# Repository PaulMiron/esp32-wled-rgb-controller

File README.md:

# ESP32 WLED RGB LED Controller

A simple controller board for **12V analog RGB LED strips** (non-addressable, common anode), built around an **ESP32 DevKitC** running **[WLED](https://kno.wled.ge/)**. It supports Wi-Fi control from the WLED app/web UI and an **IR remote** via an onboard IR receiver header.

| Assembled board | Schematic | PCB render |
|---|---|---|
|  |  |  |

## Features

- Controls 12V RGB LED strips (3 PWM channels)
- ESP32 DevKitC socketed on female headers (easy to replace/reflash)
- Logic-level MOSFETs (IRLZ44N) driven directly from 3.3V GPIO
- IR receiver input for standard 24/44-key RGB remotes
- Single 12V DC input (barrel jack); 5V for the ESP32 from an external LM2596 buck module
- Designed in KiCad

## Hardware

| Ref | Part | Notes |
|-----|------|-------|
| U1 | ESP32 DevKitC | Powered through the 5V pin |
| Q1–Q3 | IRLZ44N | Low-side switches, one per color |
| R1, R3, R5 | 220 Ω | Gate series resistors |
| R2, R4, R6 | 10 kΩ | Gate pull-downs (LEDs stay off during boot) |
| J1 | DC barrel jack | 12V input |
| J2 | 4-pin screw terminal | Connection to LM2596 module (IN+, IN−, OUT+, OUT−) |
| RGB1 | 4 solder-wire pads | +12V, G, R, B to the LED strip |
| IRRECEIVER1 | 3 solder-wire pads | VCC (3.3V), GND, OUT |
| — | LM2596 buck module | **Set output to 5V before connecting the ESP32!** |
| — | IR receiver module | e.g. VS1838B / KY-022 |

Full bill of materials: [`docs/proiectv2.csv`](docs/proiectv2.csv).

> The ESP32 footprint comes from the **Espressif KiCad library** (`PCM_Espressif`). Install it from KiCad's Plugin and Content Manager before opening the PCB.

## Pinout

| Function | ESP32 GPIO |
|----------|------------|
| Q1 (PWM) | GPIO25 |
| Q2 (PWM) | GPIO26 |
| Q3 (PWM) | GPIO33 |
| IR receiver | GPIO4 |

> Check which MOSFET drives which color on your strip and set the color order in WLED accordingly.

## WLED Configuration

1. Flash WLED to the ESP32 using the [WLED web installer](https://install.wled.me/).
2. Connect to the `WLED-AP` access point and set up your Wi-Fi.
3. Go to **Config → LED Preferences**:
   - LED type: **PWM RGB**
   - Pins: **25, 26, 33** (in R, G, B order according to your wiring)
4. Go to **Config → Sync Interfaces → Infrared**:
   - IR GPIO: **4**
   - Select your remote type (24-key, 44-key, etc.)
5. Save and reboot.

## Assembly Notes

- **Adjust the LM2596 output to 5.0V with a multimeter before plugging in the ESP32.**
- Do not power the ESP32 from USB and the 5V rail at the same time.
- Use thick wire (≥0.5 mm²) for the +12V and color channels to the LED strip.
- Without heatsinks, keep the load to roughly **3A per channel** (IRLZ44N at 3.3V gate drive).

## Known Issues (Rev 1)

- **Ground return path:** the LED current returns to the barrel jack through the LM2596 module's ground (OUT− → IN−). Fix on existing boards: solder a thick wire from the barrel jack GND pin directly to the MOSFET sources.
- **Power traces are too narrow** for high-current strips. Reinforce them with solder or copper wire.

## Planned for Rev 2

- [ ] Direct ground connection from J1 to the power ground
- [ ] Ground pour on the bottom layer
- [ ] Wider power traces (≥2 mm) for +12V and MOSFET drain/source
- [ ] Bulk capacitor (100–470 µF) on the 12V rail
- [ ] Input fuse and reverse polarity protection
- [ ] Optional onboard 5V regulator

## Repository Structure

```
├── hardware/
│   ├── proiectv2.kicad_pro      KiCad project
│   ├── proiectv2.kicad_sch      Schematic
│   └── proiectv2.kicad_pcb      PCB layout
├── gerbers/                     Gerber + drill files, ready for fabrication
├── docs/
│   └── proiectv2.csv            Bill of materials
├── images/                      Photos, schematic, PCB layout and 3D render
├── LICENSE
└── README.md
```

To order the board, zip the contents of `gerbers/` and upload the archive to any PCB manufacturer (JLCPCB, PCBWay, etc.). 2-layer, 1.6 mm, standard settings.

## License

This project is licensed under the **GNU General Public License v2.0**. See [LICENSE](LICENSE) for details.

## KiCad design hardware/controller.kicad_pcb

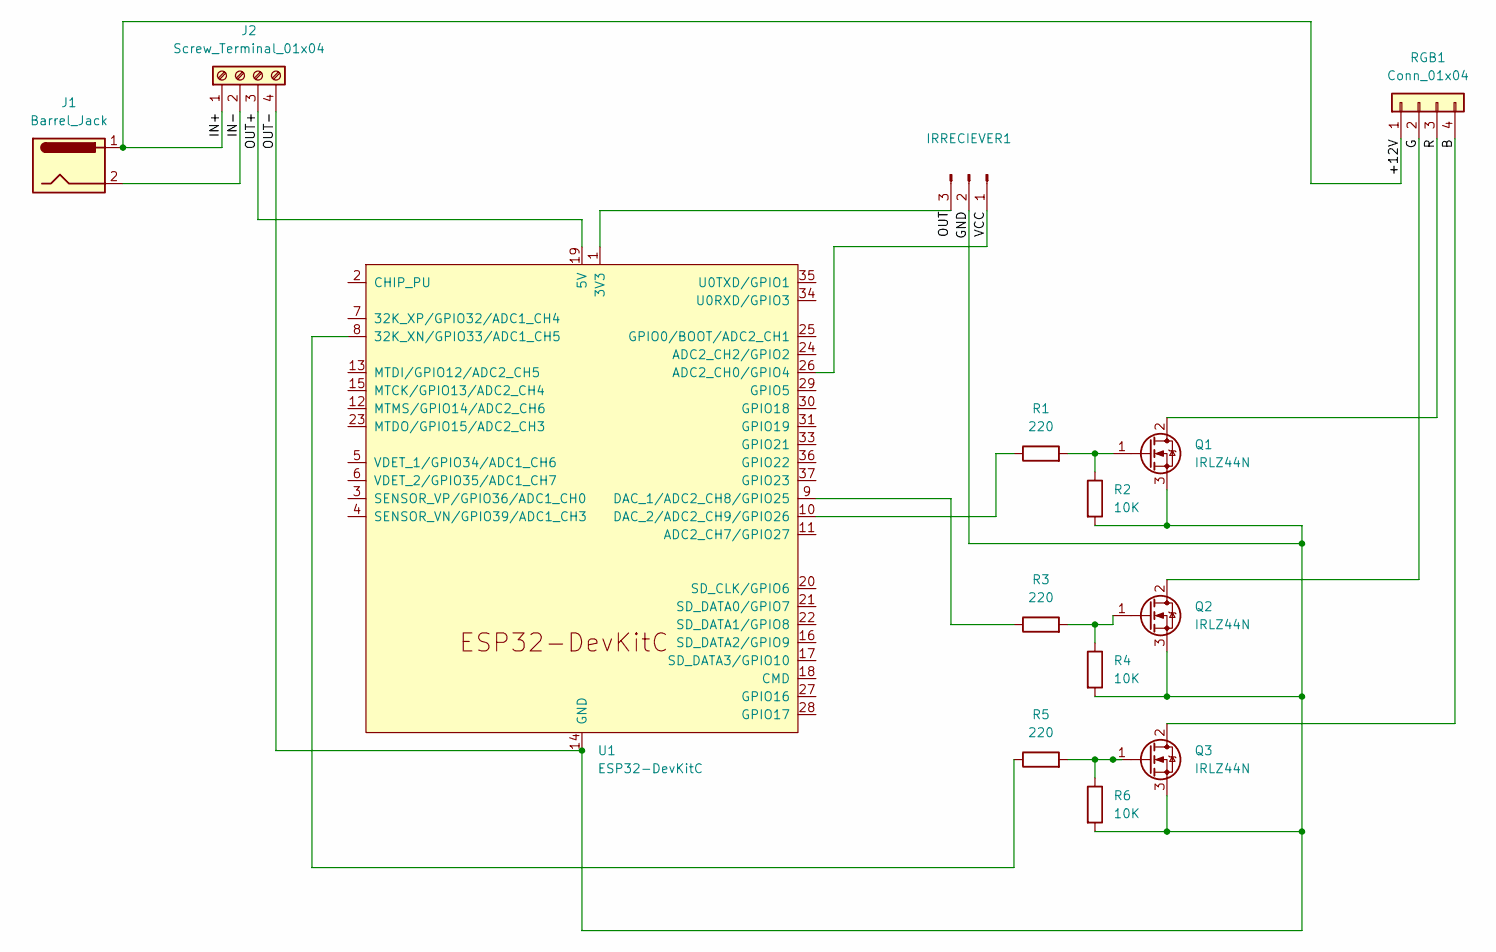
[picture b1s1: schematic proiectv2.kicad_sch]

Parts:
IRRECIEVER1: Conn_01x03_Pin; SolderWire-0.5sqmm_1x03_P4.8mm_D0.9mm_OD2.3mm
J1: Barrel_Jack; BarrelJack_Horizontal
J2: Screw_Terminal_01x04; TerminalBlock_Phoenix_MKDS-1,5-4_1x04_P5.00mm_Horizontal
Q1, Q2, Q3: IRLZ44N; TO-220-3_Vertical
R1, R3, R5: 220; R_Axial_DIN0207_L6.3mm_D2.5mm_P10.16mm_Horizontal
R2, R4, R6: 10K; R_Axial_DIN0207_L6.3mm_D2.5mm_P10.16mm_Horizontal
RGB1: Conn_01x04; SolderWire-0.5sqmm_1x04_P4.8mm_D0.9mm_OD2.3mm
U1: ESP32-DevKitC

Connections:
/+12V: J1.1, J2.1, RGB1.1; also elsewhere on the board
/B: Q3.2 (D), RGB1.4
/G: Q2.2 (D), RGB1.2
/GND: IRRECIEVER1.2, J2.4, Q1.3 (S), Q2.3 (S), Q3.3 (S), R2.2, R4.2, R6.2, U1.14 (GND), U1.32 (GND), U1.38 (GND)
/IN-: J1.2, J2.2; also elsewhere on the board
/OUT: IRRECIEVER1.3, U1.1 (3V3)
/OUT+: J2.3, U1.19 (5V)
/R: Q1.2 (D), RGB1.3
/VCC: IRRECIEVER1.1, U1.26 (ADC2_CH0/GPIO4)
unnamed: Q1.1 (G), R1.2, R2.1
unnamed: Q2.1 (G), R3.2, R4.1
unnamed: Q3.1 (G), R5.2, R6.1
unnamed: R5.1, U1.8 (32K_XN/GPIO33/ADC1_CH5)
unnamed: R3.1, U1.9 (DAC_1/ADC2_CH8/GPIO25)
unnamed: R1.1, U1.10 (DAC_2/ADC2_CH9/GPIO26)

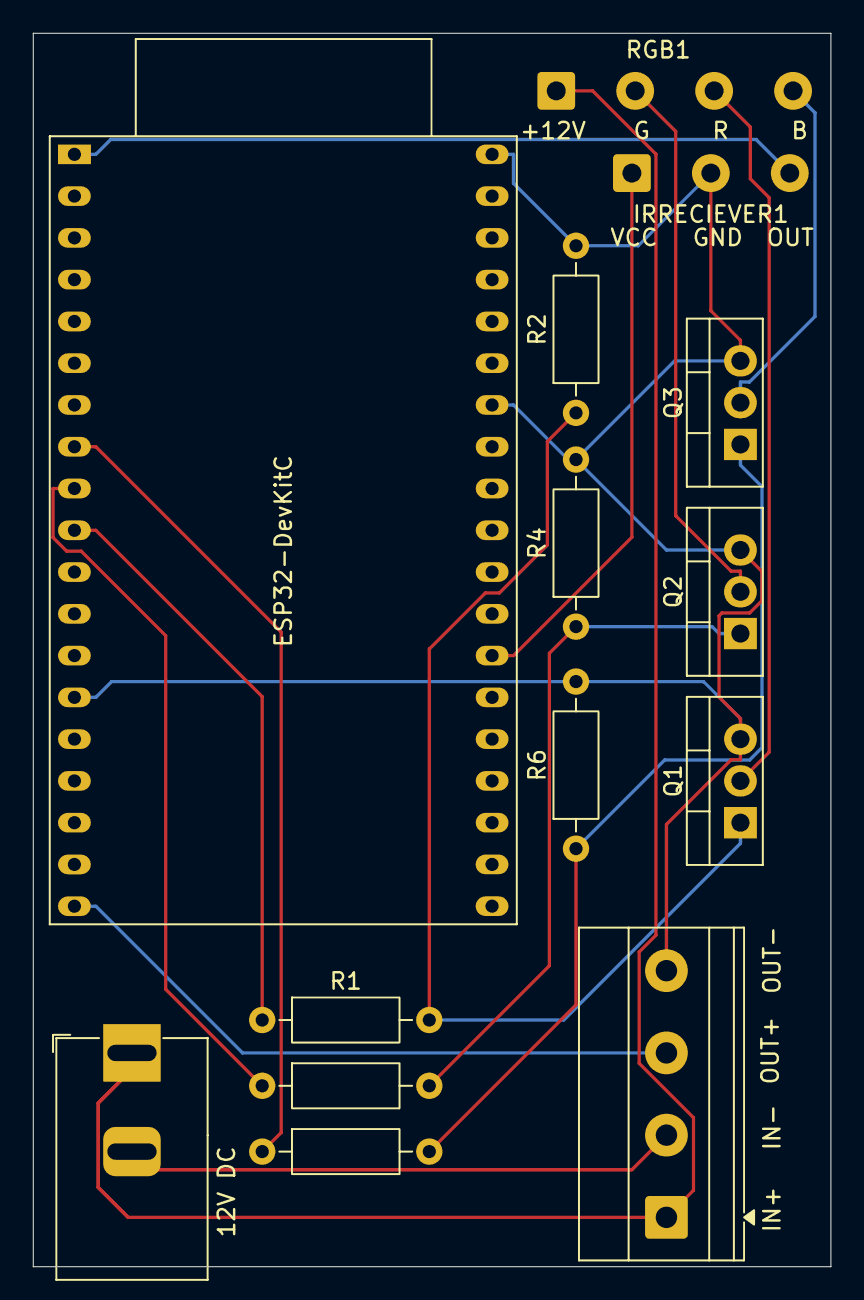
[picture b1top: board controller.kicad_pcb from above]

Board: 2 copper layers, 48.5 x 75.0 mm, 14 parts (0 on the bottom side), 15 nets.

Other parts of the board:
12V DC: Barrel_Jack; BarrelJack_Horizontal

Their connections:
/+12V: 12V DC.1; also elsewhere on the board
/IN-: 12V DC.2; also elsewhere on the board
